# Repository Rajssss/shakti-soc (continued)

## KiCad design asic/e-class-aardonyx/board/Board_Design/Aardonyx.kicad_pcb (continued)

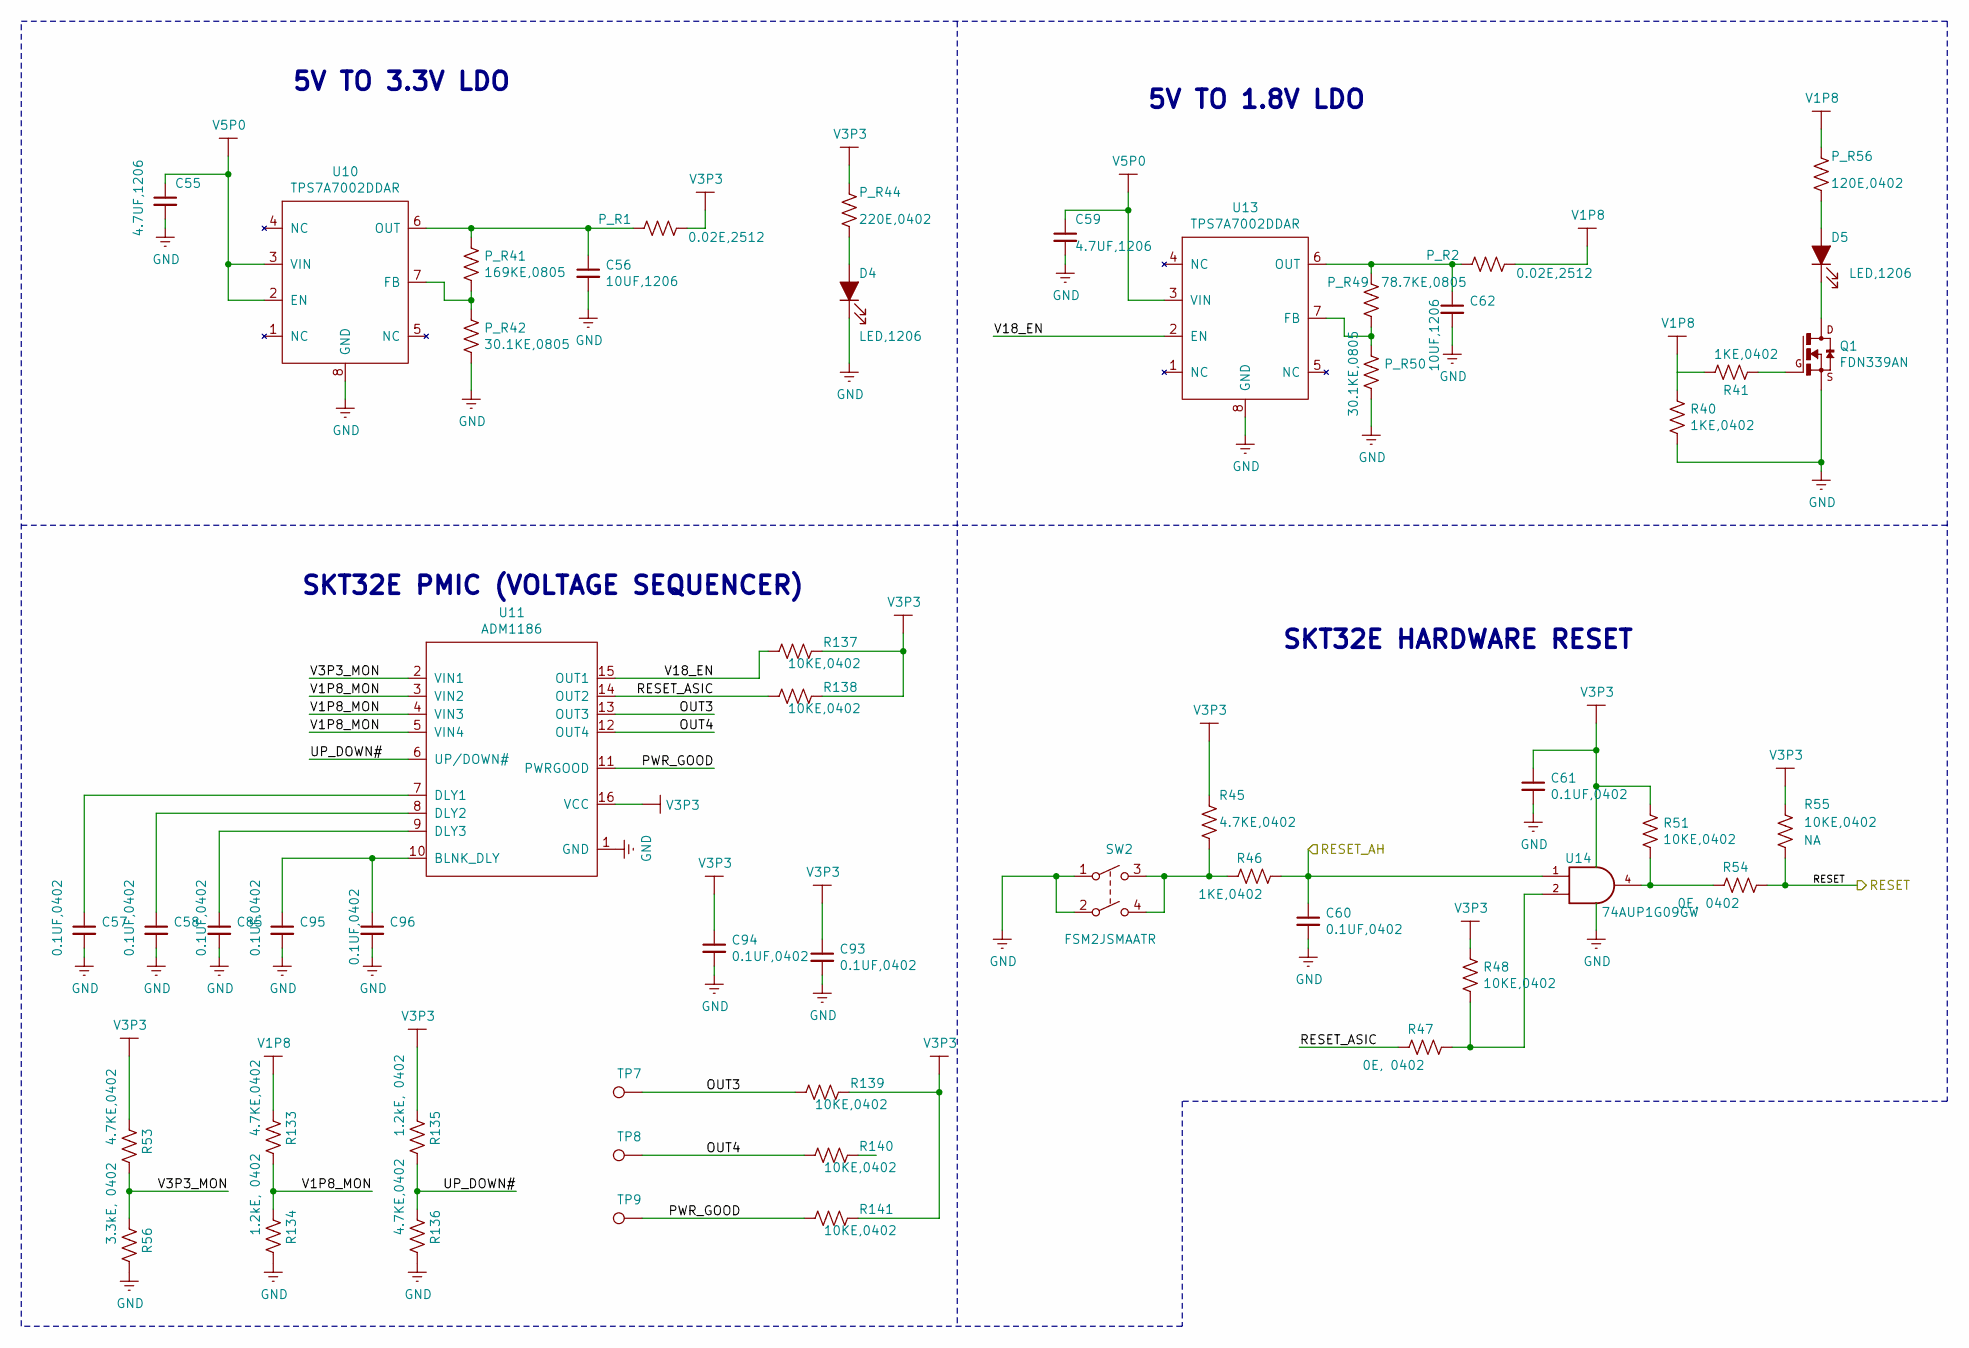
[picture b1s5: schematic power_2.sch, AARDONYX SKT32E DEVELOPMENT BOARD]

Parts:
C55, C59: 4.7UF,1206; C_1206_3216Metric; Manufactured Part Number T491A475K016AT; Digikey PartNumber 399-18027-1-ND
C56, C62: 10UF,1206; C_1206_3216Metric; Manufactured Part Number C1206C106J3RACAUTO; Digikey PartNumber 399-15734-1-ND
C57, C58, C60, C61, C85, C93, C94, C95, C96: 0.1UF,0402; C_0402_1005Metric; Manufactured Part Number 04023C104JAT2A; Digikey PartNumber 478-10050-1-ND
D4, D5: LED,1206; LED_0603_1608Metric; Manufactured Part Number SML-LX1206GW-TR; Digikey PartNumber 67-1002-1-ND
P_R1, P_R2: 0.02E,2512; R_2512_6332Metric; Manufactured Part Number PA2512FKF7W0R002E; Digikey PartNumber YAG2142CT-ND
P_R41: 169KE,0805; R_0805_2012Metric; Manufactured Part Number ERA-6AEB1693V; Digikey PartNumber P169KDACT-ND
P_R42, P_R50: 30.1KE,0805; R_0805_2012Metric; Manufactured Part Number ERA-6AEB3012V; Digikey PartNumber P30.1KDACT-ND
P_R44: 220E,0402; R_0402_1005Metric; Manufactured Part Number RC0402FR-07220RL; Digikey PartNumber 311-220LRDKR-ND
P_R49: 78.7KE,0805; R_0805_2012Metric; Manufactured Part Number ERA-6AEB7872V; Digikey PartNumber P78.7KDACT-ND
P_R56: 120E,0402; R_0402_1005Metric; Manufactured Part Number RC0402FR-07120RL; Digikey PartNumber 311-120LRCT-ND
Q1: FDN339AN; SuperSOT-3; Manufactured Part Number FDN339AN; Digikey PartNumber FDN339ANCT-ND
R40, R41, R46: 1KE,0402; R_0402_1005Metric; Manufactured Part Number ERA-2AEB123X; Digikey PartNumber P1.0KJCT-ND
R45, R53, R133, R136: 4.7KE,0402; R_0402_1005Metric; Manufactured Part Number RC0402JR-074K7L; Digikey PartNumber 311-4.7KJRCT-ND
R47, R54: 0E, 0402; R_0402_1005Metric; Manufactured Part Number CRCW04020000Z0ED; Digikey PartNumber 541-0.0JCT-ND
R48, R51, R55, R137, R138, R139, R140, R141: 10KE,0402; R_0402_1005Metric; Manufactured Part Number SG73S1ETTP103J; Digikey PartNumber 2019-SG73S1ETTP103JCT-ND
R56: 3.3kE, 0402; R_0402_1005Metric; Manufactured Part Number RC0402JR-073K3L; Digikey PartNumber 311-3.3KJRCT-ND
R134, R135: 1.2kE, 0402; R_0402_1005Metric; Manufactured Part Number RT0402DRE071K2L; Digikey PartNumber 311-2241-1-ND
SW2: FSM2JSMAATR; SW_PUSH_SPST_NO_4.5MM_7MM; Manufactured Part Number FSM2JSMAATR; Digikey PartNumber 450-1792-1-ND
TP7: OUT3; TestPoint_Pad_D1.0mm
TP8: OUT4; TestPoint_Pad_D1.0mm
TP9: POWER_GOOD; TestPoint_Pad_D1.0mm
U10, U13: TPS7A7002DDAR; SOIC-8-1EP_3.9x4.9mm_P1.27mm_EP2.29x3mm_ThermalVias; Manufactured Part Number TPS7A7002DDAR; Digikey PartNumber 296-40977-1-ND
U11: ADM1186; QSOP-16_3.9x4.9mm_P0.635mm; Manufactured Part Number ADM1186-2ARQZ; Digikey PartNumber ADM1186-2ARQZ-ND
U14: 74AUP1G09GW; SOT-353_SC-70-5_Handsoldering; Manufactured Part Number 74AUP1G09GW,125; Digikey PartNumber 1727-4492-1-ND

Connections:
/RESET: R54.2, R55.2; also elsewhere on the board
/arduino_header/RESET_AH: C60.1, R46.2, U14.1; also elsewhere on the board
/power_2/OUT3: R139.2, TP7.1, U11.13 (OUT3)
/power_2/OUT4: R140.2, TP8.1, U11.12 (OUT4)
/power_2/PWR_GOOD: R141.2, TP9.1, U11.11 (PWRGOOD)
/power_2/RESET_ASIC: R47.1, R138.2, U11.14 (OUT2)
/power_2/UP_DOWN#: R135.2, R136.1, U11.6 (UP/DOWN#)
/power_2/V1P8_MON: R133.2, R134.1, U11.3 (VIN2), U11.4 (VIN3), U11.5 (VIN4)
/power_2/V3P3_MON: R53.2, R56.1, U11.2 (VIN1)
/power_2/V18_EN: R137.2, U11.15 (OUT1), U13.2 (EN)
GND: C55.2, C56.2, C57.2, C58.2, C59.2, C60.2, C61.2, C62.2, C85.2, C93.2, C94.2, C95.2, C96.2, D4.1 (K), P_R42.2, P_R50.2, Q1.2 (S), R40.2, R56.2, R134.2, R136.2, SW2.1, SW2.2, U10.8 (GND), U11.1 (GND), U13.8 (GND), U14.3 (GND); also elsewhere on the board
unnamed: C56.1, P_R1.2, P_R41.1, U10.6 (OUT)
unnamed: C57.1, U11.7 (DLY1)
unnamed: C58.1, U11.8 (DLY2)
unnamed: C62.1, P_R2.2, P_R49.1, U13.6 (OUT)
unnamed: C85.1, U11.9 (DLY3)
unnamed: C95.1, C96.1, U11.10 (BLNK_DLY)
unnamed: D4.2 (A), P_R44.2
unnamed: D5.1 (K), Q1.3 (D)
unnamed: D5.2 (A), P_R56.2
unnamed: P_R41.2, P_R42.1, U10.7 (FB)
unnamed: P_R49.2, P_R50.1, U13.7 (FB)
unnamed: Q1.1 (G), R41.1
unnamed: R45.2, R46.1, SW2.3, SW2.4
unnamed: R47.2, R48.2, U14.2
unnamed: R51.2, R54.1, U14.4
V1P8: P_R2.1, P_R56.1, R40.1, R41.2, R133.1; also elsewhere on the board
V3P3: C61.1, C93.1, C94.1, P_R1.1, P_R44.1, R45.1, R48.1, R51.1, R53.1, R55.1, R135.1, R137.1, R138.1, R139.1, R141.1, U11.16 (VCC), U14.5 (VCC); also elsewhere on the board
V5P0: C55.1, C59.1, U10.2 (EN), U10.3 (VIN), U13.3 (VIN); also elsewhere on the board

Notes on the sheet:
SKT32E PMIC (VOLTAGE SEQUENCER)
5V TO 3.3V LDO
5V TO 1.8V LDO
SKT32E HARDWARE RESET

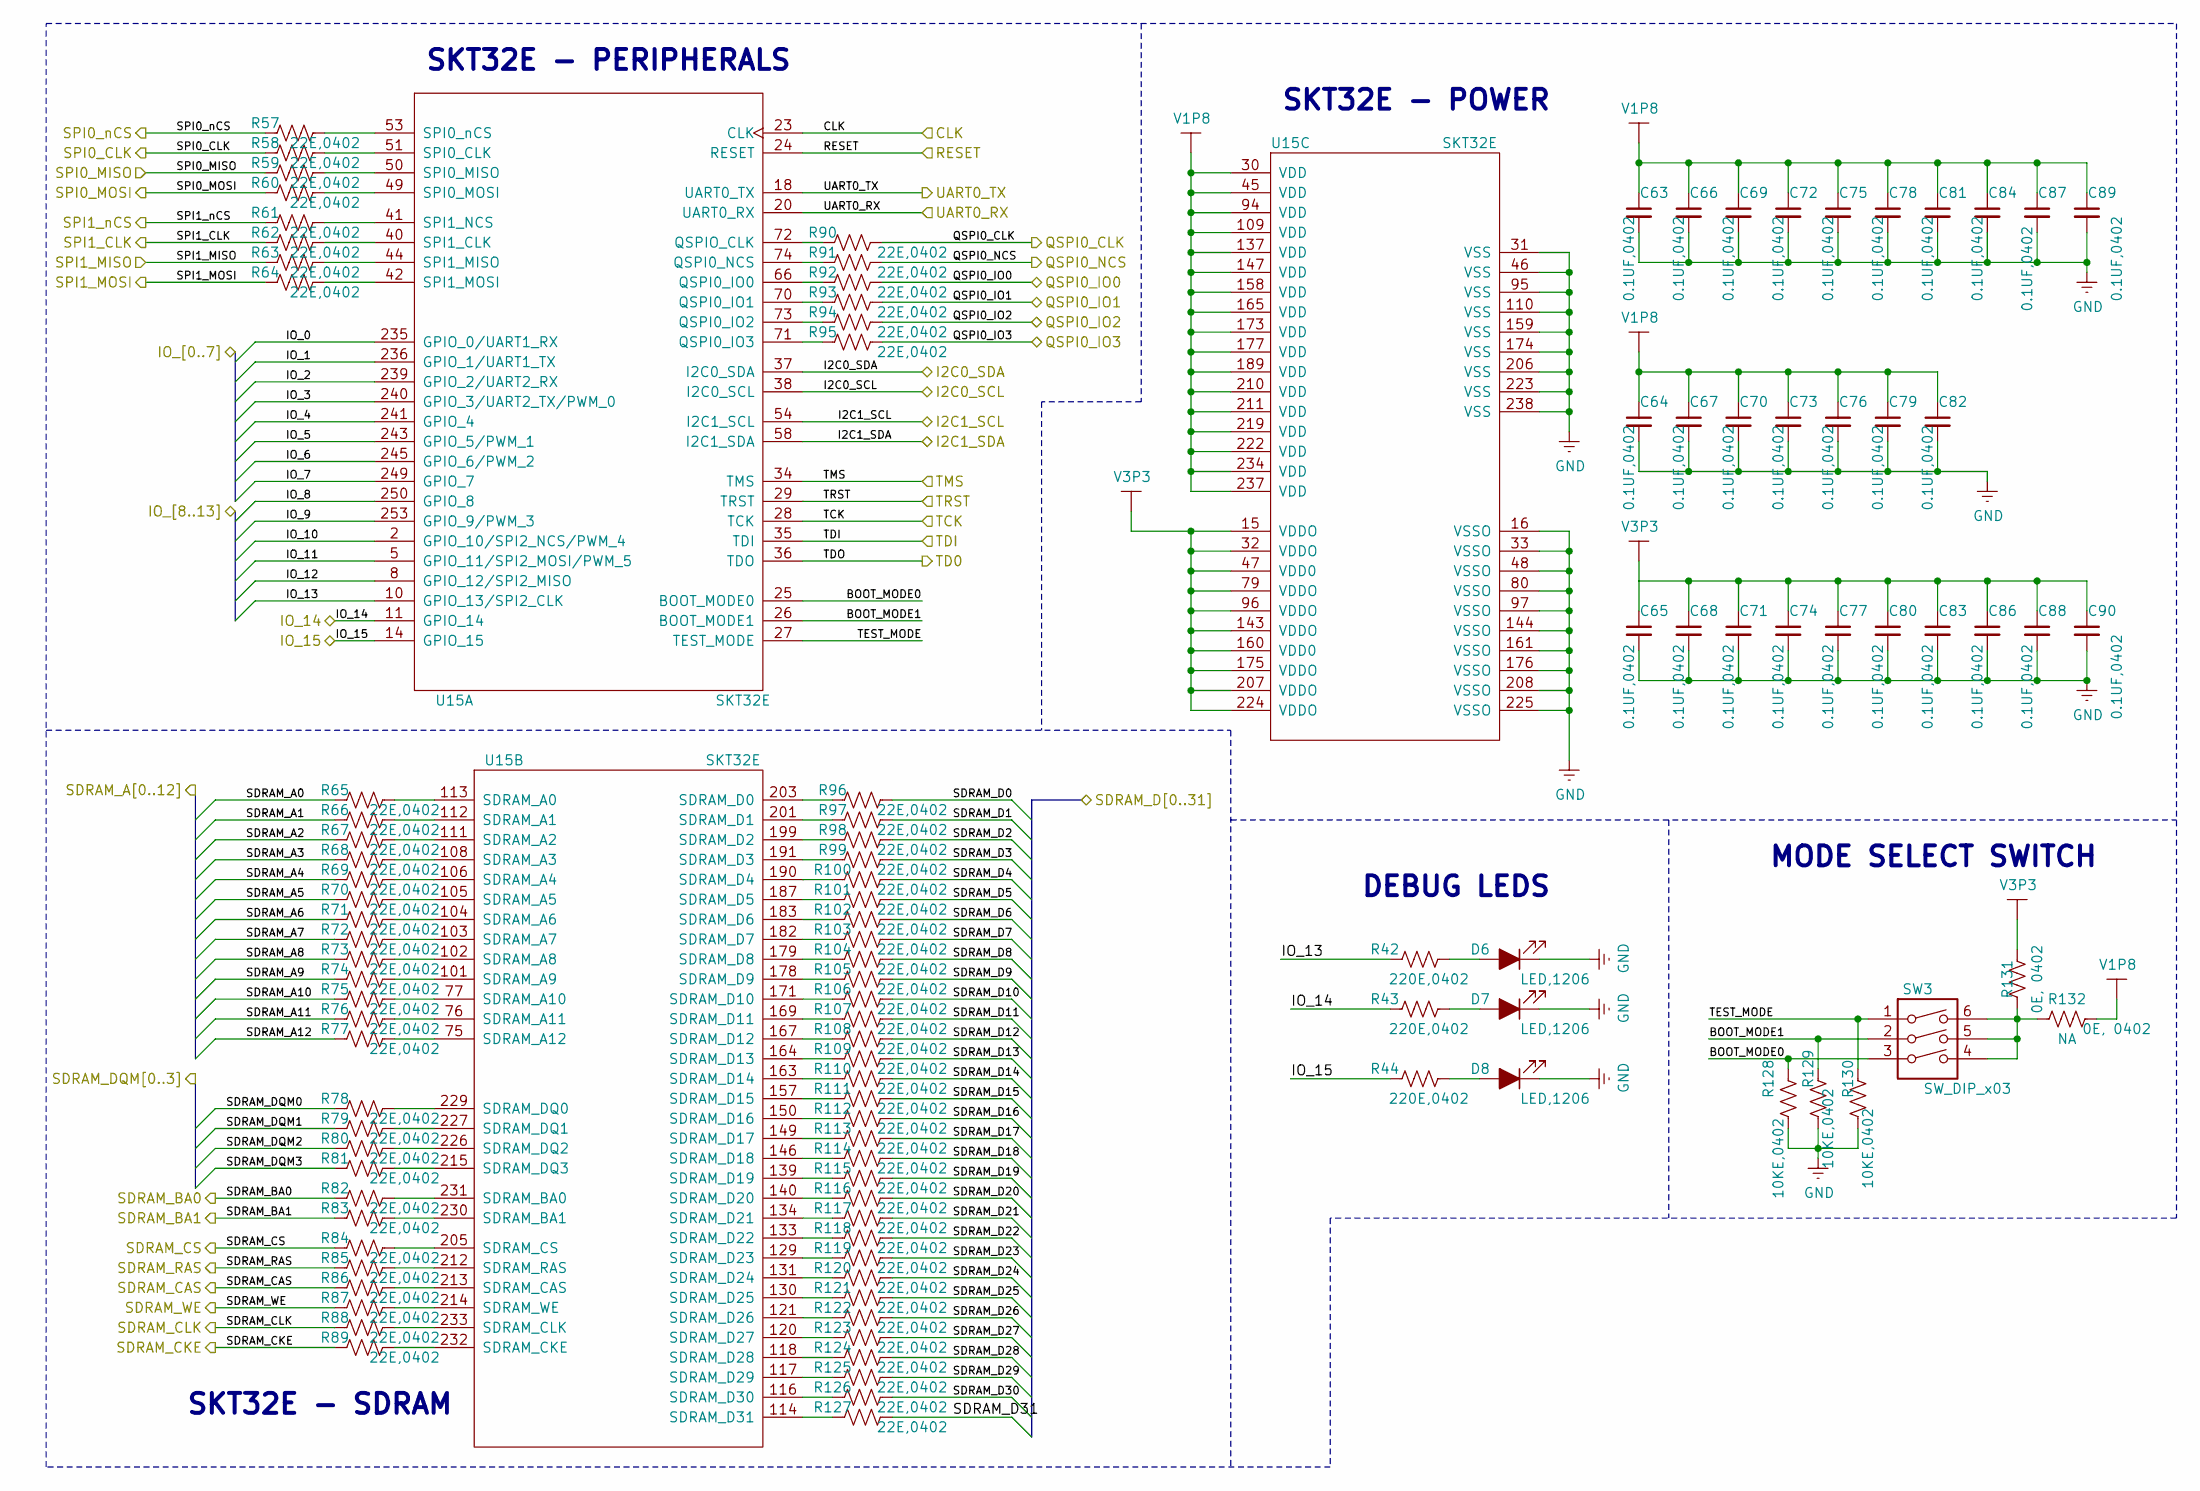
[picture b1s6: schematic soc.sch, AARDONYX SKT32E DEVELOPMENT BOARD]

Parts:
C63, C64, C65, C66, C67, C68, C69, C70, C71, C72, C73, C74, C75, C76, C77, C78, C79, C80, C81, C82, C83, C84, C86, C87, C88, C89, C90: 0.1UF,0402; C_0402_1005Metric; Manufactured Part Number 04023C104JAT2A; Digikey PartNumber 478-10050-1-ND
D6, D7, D8: LED,1206; LED_0603_1608Metric; Manufactured Part Number SML-LX1206GW-TR; Digikey PartNumber 67-1002-1-ND
R42, R43, R44: 220E,0402; R_0402_1005Metric; Manufactured Part Number RC0402FR-07220RL; Digikey PartNumber 311-220LRDKR-ND
R57, R58, R59, R60, R61, R62, R63, R64, R65, R66, R67, R68, R69, R70, R71, R72, R73, R74, R75, R76, R77, R78, R79, R80, R81, R82, R83, R84, R85, R86, R87, R88, R89, R90, R91, R92, R93, R94, R95, R96, R97, R98, R99, R100, R101, R102, R103, R104, R105, R106, R107, R108, R109, R110, R111, R112, R113, R114, R115, R116, R117, R118, R119, R120, R121, R122, R123, R124, R125, R126, R127: 22E,0402; R_0402_1005Metric; Manufactured Part Number RC0402FR-0722RL; Digikey PartNumber 311-22.0LRCT-ND
R128, R129, R130: 10KE,0402; R_0402_1005Metric; Manufactured Part Number SG73S1ETTP103J; Digikey PartNumber 2019-SG73S1ETTP103JCT-ND
R131, R132: 0E, 0402; R_0402_1005Metric; Manufactured Part Number CRCW04020000Z0ED; Digikey PartNumber 541-0.0JCT-ND
SW3: SW_DIP_x03; SW_DIP_SPSTx03_Slide_6.7x9.18mm_W7.62mm_P2.54mm_LowProfile; Manufactured Part Number 418117270903; Digikey PartNumber 732-3833-5-ND
U15: SKT32E; SKT32E_IITM; Manufactured Part Number SKT32E; Digikey PartNumber NA

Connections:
/RESET: U15.24 (RESET); also elsewhere on the board
/arduino_header/I2C0_SCL: U15.38 (I2C0_SCL); also elsewhere on the board
/arduino_header/I2C0_SDA: U15.37 (I2C0_SDA); also elsewhere on the board
/arduino_header/I2C1_SCL: U15.54 (I2C1_SCL); also elsewhere on the board
/arduino_header/I2C1_SDA: U15.58 (I2C1_SDA); also elsewhere on the board
/arduino_header/IO_0: U15.235 (GPIO_0/UART1_RX); also elsewhere on the board
/arduino_header/IO_1: U15.236 (GPIO_1/UART1_TX); also elsewhere on the board
/arduino_header/IO_2: U15.239 (GPIO_2/UART2_RX); also elsewhere on the board
/arduino_header/IO_3: U15.240 (GPIO_3/UART2_TX/PWM_0); also elsewhere on the board
/arduino_header/IO_4: U15.241 (GPIO_4); also elsewhere on the board
/arduino_header/IO_5: U15.243 (GPIO_5/PWM_1); also elsewhere on the board
/arduino_header/IO_6: U15.245 (GPIO_6/PWM_2); also elsewhere on the board
/arduino_header/IO_7: U15.249 (GPIO_7); also elsewhere on the board
/arduino_header/IO_8: U15.250 (GPIO_8); also elsewhere on the board
/arduino_header/IO_9: U15.253 (GPIO_9/PWM_3); also elsewhere on the board
/arduino_header/IO_10: U15.2 (GPIO_10/SPI2_NCS/PWM_4); also elsewhere on the board
/arduino_header/IO_11: U15.5 (GPIO_11/SPI2_MOSI/PWM_5); also elsewhere on the board
/arduino_header/IO_12: U15.8 (GPIO_12/SPI2_MISO); also elsewhere on the board
/arduino_header/IO_13: R42.1, U15.10 (GPIO_13/SPI2_CLK); also elsewhere on the board
/arduino_header/IO_14: R43.1, U15.11 (GPIO_14); also elsewhere on the board
/arduino_header/IO_15: R44.1, U15.14 (GPIO_15); also elsewhere on the board
/arduino_header/QSPI0_CLK: R90.1; also elsewhere on the board
/arduino_header/QSPI0_IO0: R93.1; also elsewhere on the board
/arduino_header/QSPI0_IO2: R94.1; also elsewhere on the board
/arduino_header/QSPI0_IO3: R95.1; also elsewhere on the board
/arduino_header/QSPI0_NCS: R91.1; also elsewhere on the board
/arduino_header/SPI0_CLK: R58.2; also elsewhere on the board
/arduino_header/SPI0_MISO: R59.2; also elsewhere on the board
/arduino_header/SPI0_MOSI: R60.2; also elsewhere on the board
/arduino_header/SPI0_nCS: R57.2; also elsewhere on the board
/arduino_header/SPI1_CLK: R62.2; also elsewhere on the board
/arduino_header/SPI1_MISO: R63.2; also elsewhere on the board
/arduino_header/SPI1_MOSI: R64.2; also elsewhere on the board
/arduino_header/SPI1_nCS: R61.2; also elsewhere on the board
/ftdi/TCK: U15.28 (TCK); also elsewhere on the board
/ftdi/TDI: U15.35 (TDI); also elsewhere on the board
/ftdi/TMS: U15.34 (TMS); also elsewhere on the board
/ftdi/TRST: U15.29 (TRST); also elsewhere on the board
/ftdi/UART0_RX: U15.20 (UART0_RX); also elsewhere on the board
/ftdi/UART0_TX: U15.18 (UART0_TX); also elsewhere on the board
/sdram/CLK: U15.23 (CLK); also elsewhere on the board
/sdram/SDRAM_A0: R65.2; also elsewhere on the board
/sdram/SDRAM_A1: R66.2; also elsewhere on the board
/sdram/SDRAM_A2: R67.2; also elsewhere on the board
/sdram/SDRAM_A3: R68.2; also elsewhere on the board
/sdram/SDRAM_A4: R69.2; also elsewhere on the board
/sdram/SDRAM_A5: R70.2; also elsewhere on the board
/sdram/SDRAM_A6: R71.2; also elsewhere on the board
/sdram/SDRAM_A7: R72.2; also elsewhere on the board
/sdram/SDRAM_A8: R73.2; also elsewhere on the board
/sdram/SDRAM_A9: R74.2; also elsewhere on the board
/sdram/SDRAM_A10: R75.2; also elsewhere on the board
/sdram/SDRAM_A11: R76.2; also elsewhere on the board
/sdram/SDRAM_A12: R77.2; also elsewhere on the board
/sdram/SDRAM_BA0: R82.2; also elsewhere on the board
/sdram/SDRAM_BA1: R83.2; also elsewhere on the board
/sdram/SDRAM_CAS: R86.2; also elsewhere on the board
/sdram/SDRAM_CKE: R89.2; also elsewhere on the board
/sdram/SDRAM_CLK: R88.2; also elsewhere on the board
/sdram/SDRAM_CS: R84.2; also elsewhere on the board
/sdram/SDRAM_D0: R96.1; also elsewhere on the board
/sdram/SDRAM_D1: R97.1; also elsewhere on the board
/sdram/SDRAM_D2: R98.1; also elsewhere on the board
/sdram/SDRAM_D3: R99.1; also elsewhere on the board
/sdram/SDRAM_D4: R100.1; also elsewhere on the board
/sdram/SDRAM_D5: R101.1; also elsewhere on the board
/sdram/SDRAM_D6: R102.1; also elsewhere on the board
/sdram/SDRAM_D7: R103.1; also elsewhere on the board
/sdram/SDRAM_D8: R104.1; also elsewhere on the board
/sdram/SDRAM_D9: R105.1; also elsewhere on the board
/sdram/SDRAM_D10: R106.1; also elsewhere on the board
/sdram/SDRAM_D11: R107.1; also elsewhere on the board
/sdram/SDRAM_D12: R108.1; also elsewhere on the board
/sdram/SDRAM_D13: R109.1; also elsewhere on the board
/sdram/SDRAM_D14: R110.1; also elsewhere on the board
/sdram/SDRAM_D15: R111.1; also elsewhere on the board
/sdram/SDRAM_D16: R112.1; also elsewhere on the board
/sdram/SDRAM_D17: R113.1; also elsewhere on the board
/sdram/SDRAM_D18: R114.1; also elsewhere on the board
/sdram/SDRAM_D19: R115.1; also elsewhere on the board
/sdram/SDRAM_D20: R116.1; also elsewhere on the board
/sdram/SDRAM_D21: R117.1; also elsewhere on the board
/sdram/SDRAM_D22: R118.1; also elsewhere on the board
/sdram/SDRAM_D23: R119.1; also elsewhere on the board
/sdram/SDRAM_D24: R120.1; also elsewhere on the board
/sdram/SDRAM_D25: R121.1; also elsewhere on the board
/sdram/SDRAM_D26: R122.1; also elsewhere on the board
/sdram/SDRAM_D27: R123.1; also elsewhere on the board
/sdram/SDRAM_D28: R124.1; also elsewhere on the board
/sdram/SDRAM_D29: R125.1; also elsewhere on the board
/sdram/SDRAM_D30: R126.1; also elsewhere on the board
/sdram/SDRAM_D31: R127.1; also elsewhere on the board
/sdram/SDRAM_DQM0: R78.2; also elsewhere on the board
/sdram/SDRAM_DQM1: R79.2; also elsewhere on the board
/sdram/SDRAM_DQM2: R80.2; also elsewhere on the board
/sdram/SDRAM_DQM3: R81.2; also elsewhere on the board
/sdram/SDRAM_RAS: R85.2; also elsewhere on the board
/sdram/SDRAM_WE: R87.2; also elsewhere on the board
/soc/BOOT_MODE0: R128.1, SW3.3, U15.25 (BOOT_MODE0)
/soc/BOOT_MODE1: R129.1, SW3.2, U15.26 (BOOT_MODE1)
/soc/QSPI0_IO0: R92.1; also elsewhere on the board
/soc/TD0: U15.36 (TDO); also elsewhere on the board
/soc/TEST_MODE: R130.1, SW3.1, U15.27 (TEST_MODE)
GND: C63.2, C64.2, C65.2, C66.2, C67.2, C68.2, C69.2, C70.2, C71.2, C72.2, C73.2, C74.2, C75.2, C76.2, C77.2, C78.2, C79.2, C80.2, C81.2, C82.2, C83.2, C84.2, C86.2, C87.2, C88.2, C89.2, C90.2, D6.1 (K), D7.1 (K), D8.1 (K), R128.2, R129.2, R130.2, U15.16 (VSSO), U15.31 (VSS), U15.33 (VSSO), U15.46 (VSS), U15.48 (VSSO), U15.80 (VSSO), U15.95 (VSS), U15.97 (VSSO), U15.110 (VSS), U15.144 (VSSO), U15.159 (VSS), U15.161 (VSSO), U15.174 (VSS), U15.176 (VSSO), U15.206 (VSS), U15.208 (VSSO), U15.223 (VSS), U15.225 (VSSO), U15.238 (VSS); also elsewhere on the board
unnamed: D6.2 (A), R42.2
unnamed: D7.2 (A), R43.2
unnamed: D8.2 (A), R44.2
unnamed: R57.1, U15.53 (SPI0_nCS)
unnamed: R58.1, U15.51 (SPI0_CLK)
unnamed: R59.1, U15.50 (SPI0_MISO)
unnamed: R60.1, U15.49 (SPI0_MOSI)
unnamed: R61.1, U15.41 (SPI1_NCS)
unnamed: R62.1, U15.40 (SPI1_CLK)
unnamed: R63.1, U15.44 (SPI1_MISO)
unnamed: R64.1, U15.42 (SPI1_MOSI)
unnamed: R65.1, U15.113 (SDRAM_A0)
unnamed: R66.1, U15.112 (SDRAM_A1)
unnamed: R67.1, U15.111 (SDRAM_A2)
unnamed: R68.1, U15.108 (SDRAM_A3)
unnamed: R69.1, U15.106 (SDRAM_A4)
unnamed: R70.1, U15.105 (SDRAM_A5)
unnamed: R71.1, U15.104 (SDRAM_A6)
unnamed: R72.1, U15.103 (SDRAM_A7)
unnamed: R73.1, U15.102 (SDRAM_A8)
unnamed: R74.1, U15.101 (SDRAM_A9)
unnamed: R75.1, U15.77 (SDRAM_A10)
unnamed: R76.1, U15.76 (SDRAM_A11)
unnamed: R77.1, U15.75 (SDRAM_A12)
unnamed: R78.1, U15.229 (SDRAM_DQ0)
unnamed: R79.1, U15.227 (SDRAM_DQ1)
unnamed: R80.1, U15.226 (SDRAM_DQ2)
unnamed: R81.1, U15.215 (SDRAM_DQ3)
unnamed: R82.1, U15.231 (SDRAM_BA0)
unnamed: R83.1, U15.230 (SDRAM_BA1)
unnamed: R84.1, U15.205 (SDRAM_CS)
unnamed: R85.1, U15.212 (SDRAM_RAS)
unnamed: R86.1, U15.213 (SDRAM_CAS)
unnamed: R87.1, U15.214 (SDRAM_WE)
unnamed: R88.1, U15.233 (SDRAM_CLK)
unnamed: R89.1, U15.232 (SDRAM_CKE)
unnamed: R90.2, U15.72 (QSPIO_CLK)
unnamed: R91.2, U15.74 (QSPI0_NCS)
unnamed: R92.2, U15.66 (QSPI0_IO0)
unnamed: R93.2, U15.70 (QSPI0_IO1)
unnamed: R94.2, U15.73 (QSPI0_IO2)
unnamed: R95.2, U15.71 (QSPI0_IO3)
unnamed: R96.2, U15.203 (SDRAM_D0)
unnamed: R97.2, U15.201 (SDRAM_D1)
unnamed: R98.2, U15.199 (SDRAM_D2)
unnamed: R99.2, U15.191 (SDRAM_D3)
unnamed: R100.2, U15.190 (SDRAM_D4)
unnamed: R101.2, U15.187 (SDRAM_D5)
unnamed: R102.2, U15.183 (SDRAM_D6)
unnamed: R103.2, U15.182 (SDRAM_D7)
unnamed: R104.2, U15.179 (SDRAM_D8)
unnamed: R105.2, U15.178 (SDRAM_D9)
unnamed: R106.2, U15.171 (SDRAM_D10)
unnamed: R107.2, U15.169 (SDRAM_D11)
unnamed: R108.2, U15.167 (SDRAM_D12)
unnamed: R109.2, U15.164 (SDRAM_D13)
unnamed: R110.2, U15.163 (SDRAM_D14)
unnamed: R111.2, U15.157 (SDRAM_D15)
unnamed: R112.2, U15.150 (SDRAM_D16)
unnamed: R113.2, U15.149 (SDRAM_D17)
unnamed: R114.2, U15.146 (SDRAM_D18)
unnamed: R115.2, U15.139 (SDRAM_D19)
unnamed: R116.2, U15.140 (SDRAM_D20)
unnamed: R117.2, U15.134 (SDRAM_D21)
unnamed: R118.2, U15.133 (SDRAM_D22)
unnamed: R119.2, U15.129 (SDRAM_D23)
unnamed: R120.2, U15.131 (SDRAM_D24)
unnamed: R121.2, U15.130 (SDRAM_D25)
unnamed: R122.2, U15.121 (SDRAM_D26)
unnamed: R123.2, U15.120 (SDRAM_D27)
unnamed: R124.2, U15.118 (SDRAM_D28)
unnamed: R125.2, U15.117 (SDRAM_D29)
unnamed: R126.2, U15.116 (SDRAM_D30)
unnamed: R127.2, U15.114 (SDRAM_D31)
unnamed: R131.2, R132.2, SW3.4, SW3.5, SW3.6
V1P8: C63.1, C64.1, C66.1, C67.1, C69.1, C70.1, C72.1, C73.1, C75.1, C76.1, C78.1, C79.1, C81.1, C82.1, C84.1, C87.1, C89.1, R132.1, U15.30 (VDD), U15.45 (VDD), U15.94 (VDD), U15.109 (VDD), U15.137 (VDD), U15.147 (VDD), U15.158 (VDD), U15.165 (VDD), U15.173 (VDD), U15.177 (VDD), U15.189 (VDD), U15.210 (VDD), U15.211 (VDD), U15.219 (VDD), U15.222 (VDD), U15.234 (VDD), U15.237 (VDD); also elsewhere on the board
V3P3: C65.1, C68.1, C71.1, C74.1, C77.1, C80.1, C83.1, C86.1, C88.1, C90.1, R131.1, U15.15 (VDDO), U15.32 (VDDO), U15.47 (VDD0), U15.79 (VDDO), U15.96 (VDDO), U15.143 (VDDO), U15.160 (VDD0), U15.175 (VDDO), U15.207 (VDDO), U15.224 (VDDO); also elsewhere on the board

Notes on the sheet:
SKT32E - POWER
SKT32E - SDRAM
SKT32E - PERIPHERALS
MODE SELECT SWITCH
DEBUG LEDS

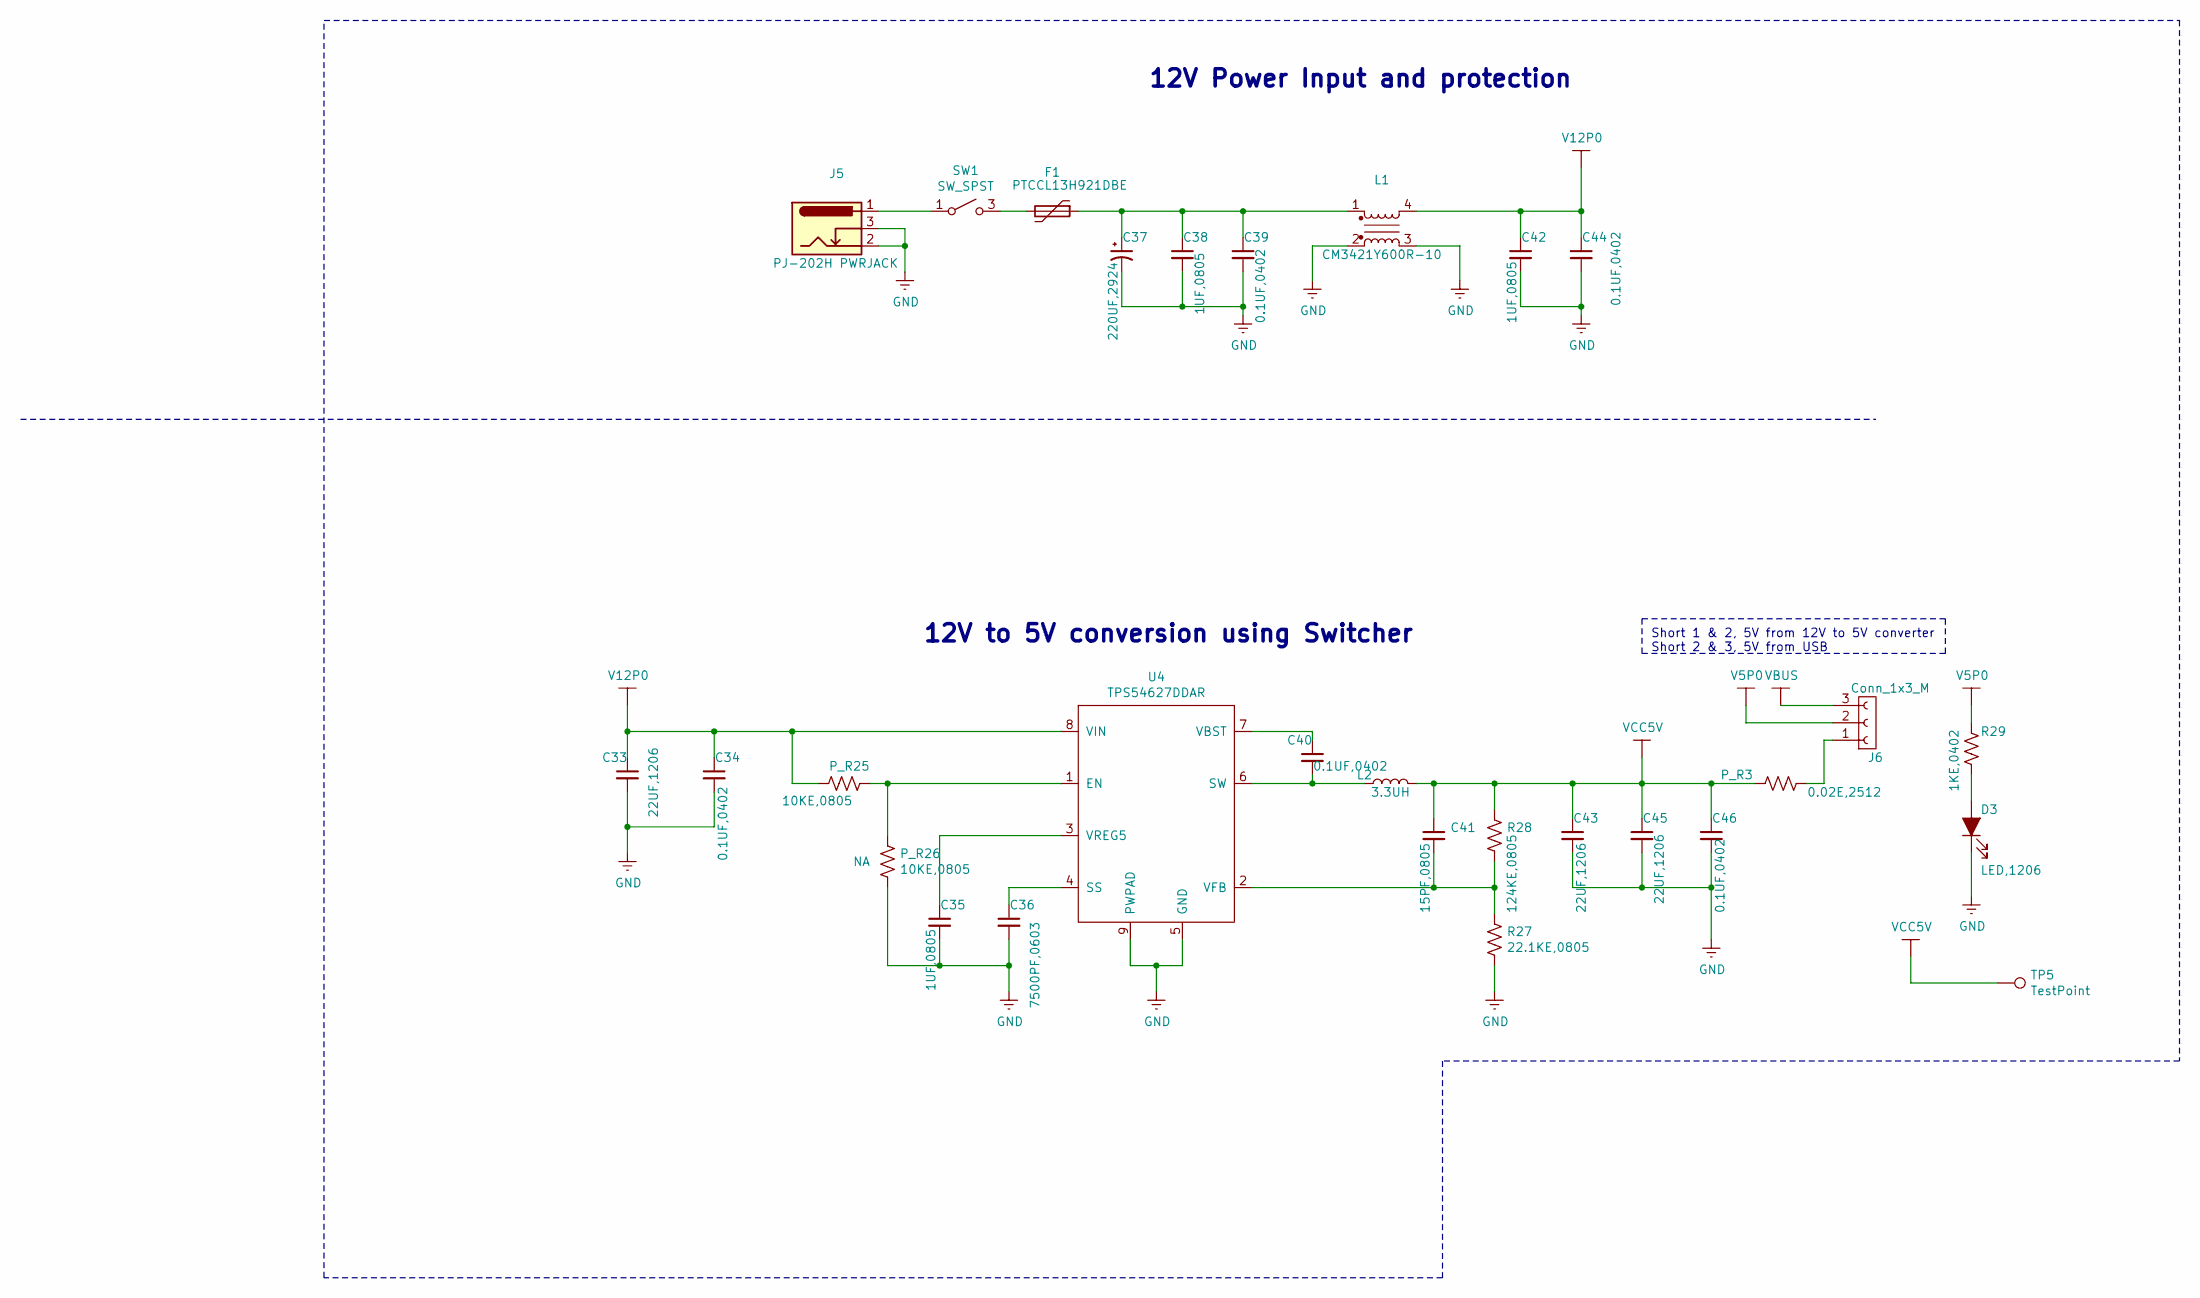
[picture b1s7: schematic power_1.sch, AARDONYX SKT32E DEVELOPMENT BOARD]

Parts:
C33, C43, C45: 22UF,1206; C_1206_3216Metric; Manufactured Part Number CL31A226KAHNNNE; Digikey PartNumber 1276-3047-1-ND
C34, C39, C40, C44, C46: 0.1UF,0402; C_0402_1005Metric; Manufactured Part Number 04023C104JAT2A; Digikey PartNumber 478-10050-1-ND
C35, C38, C42: 1UF,0805; C_0805_2012Metric; Manufactured Part Number C0805C105J3RACTU; Digikey PartNumber 399-10060-6-ND
C36: 7500PF,0603; C_0603_1608Metric; Manufactured Part Number C0603C752J3GAC7867; Digikey PartNumber 399-9980-1-ND
C37: 220UF,2924; CP_EIA-7260-38_VISHAY_Pad2.68x7.50mm_HandSolder; Manufactured Part Number TCN4227M025R0100; Digikey PartNumber 478-12518-1-ND
C41: 15PF,0805; C_0805_2012Metric; Manufactured Part Number 885012007029; Digikey PartNumber 732-7828-1-ND
D3: LED,1206; LED_0603_1608Metric; Manufactured Part Number SML-LX1206GW-TR; Digikey PartNumber 67-1002-1-ND
F1: PTCCL13H921DBE; vishay_ptccl_d1mm_w5mm; Manufactured Part Number PTCCL13H921DBE; Digikey PartNumber BC2323-ND
J5: PJ-202H PWRJACK; Pwr_Jack_DC_PJ-202AH_Horizontal; Manufactured Part Number PJ-202AH; Digikey PartNumber CP-202AH-ND
J6: Conn_1x3_M; PinHeader_1x03_P2.54mm_Vertical; Manufactured Part Number 68000-203HLF; Digikey PartNumber 609-3464-ND
L1: CM3421Y600R-10; L_Laird_L9.55_W2.84; Manufactured Part Number CM3421Y600R-10; Digikey PartNumber 240-2501-1-ND
L2: 3.3UH; Bourns_srn8040ta_L8.5_W6.6; Manufactured Part Number SRN8040TA-3R3Y; Digikey PartNumber SRN8040TA-3R3YCT-ND
P_R3: 0.02E,2512; R_2512_6332Metric; Manufactured Part Number PA2512FKF7W0R002E; Digikey PartNumber YAG2142CT-ND
P_R25, P_R26: 10KE,0805; R_0805_2012Metric; Manufactured Part Number RC0805FR-0710KL; Digikey PartNumber 311-10.0KCRCT-ND
R27: 22.1KE,0805; R_0805_2012Metric; Manufactured Part Number ERA-6AEB2212V; Digikey PartNumber P22.1KDACT-ND
R28: 124KE,0805; R_0805_2012Metric; Manufactured Part Number ERJ-6ENF1243V; Digikey PartNumber P124KCCT-ND
R29: 1KE,0402; R_0402_1005Metric; Manufactured Part Number ERA-2AEB123X; Digikey PartNumber P1.0KJCT-ND
SW1: SW_SPST; SW_toggle_spst_2.54mm; Manufactured Part Number TMS6T1B1M1QE (2267080-1); Digikey PartNumber TMS6T1B1M1QE
TP5: TestPoint; TestPoint_Pad_D1.0mm
U4: TPS54627DDAR; SOIC-8-1EP_3.9x4.9mm_P1.27mm_EP2.29x3mm_ThermalVias; Manufactured Part Number TPS54627DDAR; Digikey PartNumber 296-40808-1-ND

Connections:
GND: C33.2, C34.2, C35.2, C36.2, C37.2, C38.2, C39.2, C42.2, C43.2, C44.2, C45.2, C46.2, D3.1 (K), J5.2, J5.3, L1.2, L1.3, P_R26.2, R27.2, U4.5 (GND), U4.9 (PWPAD); also elsewhere on the board
unnamed: C35.1, U4.3 (VREG5)
unnamed: C36.1, U4.4 (SS)
unnamed: C37.1, C38.1, C39.1, F1.1, L1.1
unnamed: C40.1, U4.7 (VBST)
unnamed: C40.2, L2.1, U4.6 (SW)
unnamed: C41.2, R27.1, R28.2, U4.2 (VFB)
unnamed: D3.2 (A), R29.2
unnamed: F1.2, SW1.3 (B)
unnamed: J5.1, SW1.1 (A)
unnamed: J6.1, P_R3.1
unnamed: P_R25.2, P_R26.1, U4.1 (EN)
V5P0: J6.2, R29.1; also elsewhere on the board
V12P0: C33.1, C34.1, C42.1, C44.1, L1.4, P_R25.1, U4.8 (VIN)
VBUS: J6.3; also elsewhere on the board
VCC5V: C41.1, C43.1, C45.1, C46.1, L2.2, P_R3.2, R28.1, TP5.1

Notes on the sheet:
12V to 5V conversion using Switcher
12V Power Input and protection
Short 1 & 2, 5V from 12V to 5V converter Short 2 & 3, 5V from USB
